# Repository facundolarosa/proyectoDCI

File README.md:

# proyectoDCI
Proyecto de la materia "Diseño de circuitos impresos"

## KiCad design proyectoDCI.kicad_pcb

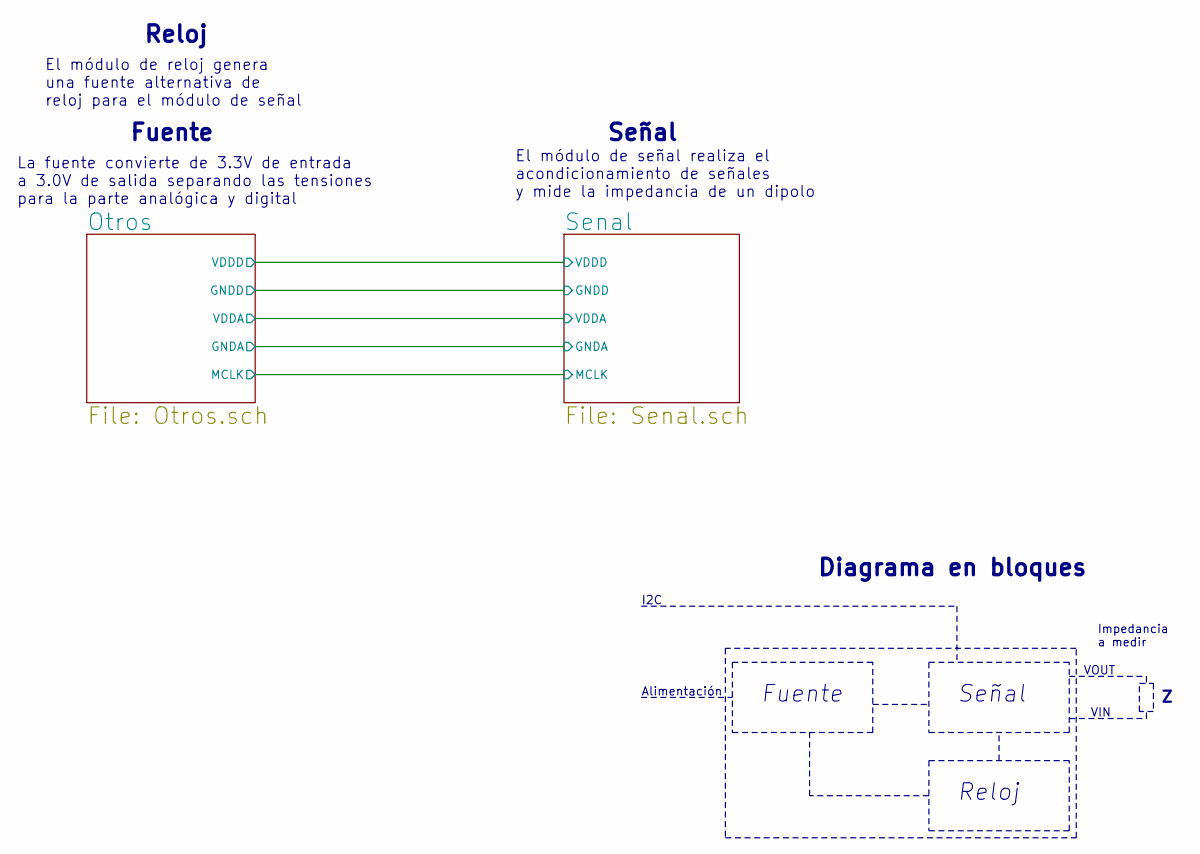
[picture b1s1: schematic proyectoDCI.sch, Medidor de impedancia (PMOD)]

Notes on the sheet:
Diagrama en bloques
Fuente
Señal
Reloj
VOUT
VIN
Impedancia a medir
I2C
La fuente convierte de 3.3V de entrada a 3.0V de salida separando las tensiones para la parte analógica y digital
El módulo de señal realiza el acondicionamiento de señales y mide la impedancia de un dipolo
El módulo de reloj genera una fuente alternativa de reloj para el módulo de señal
Alimentación

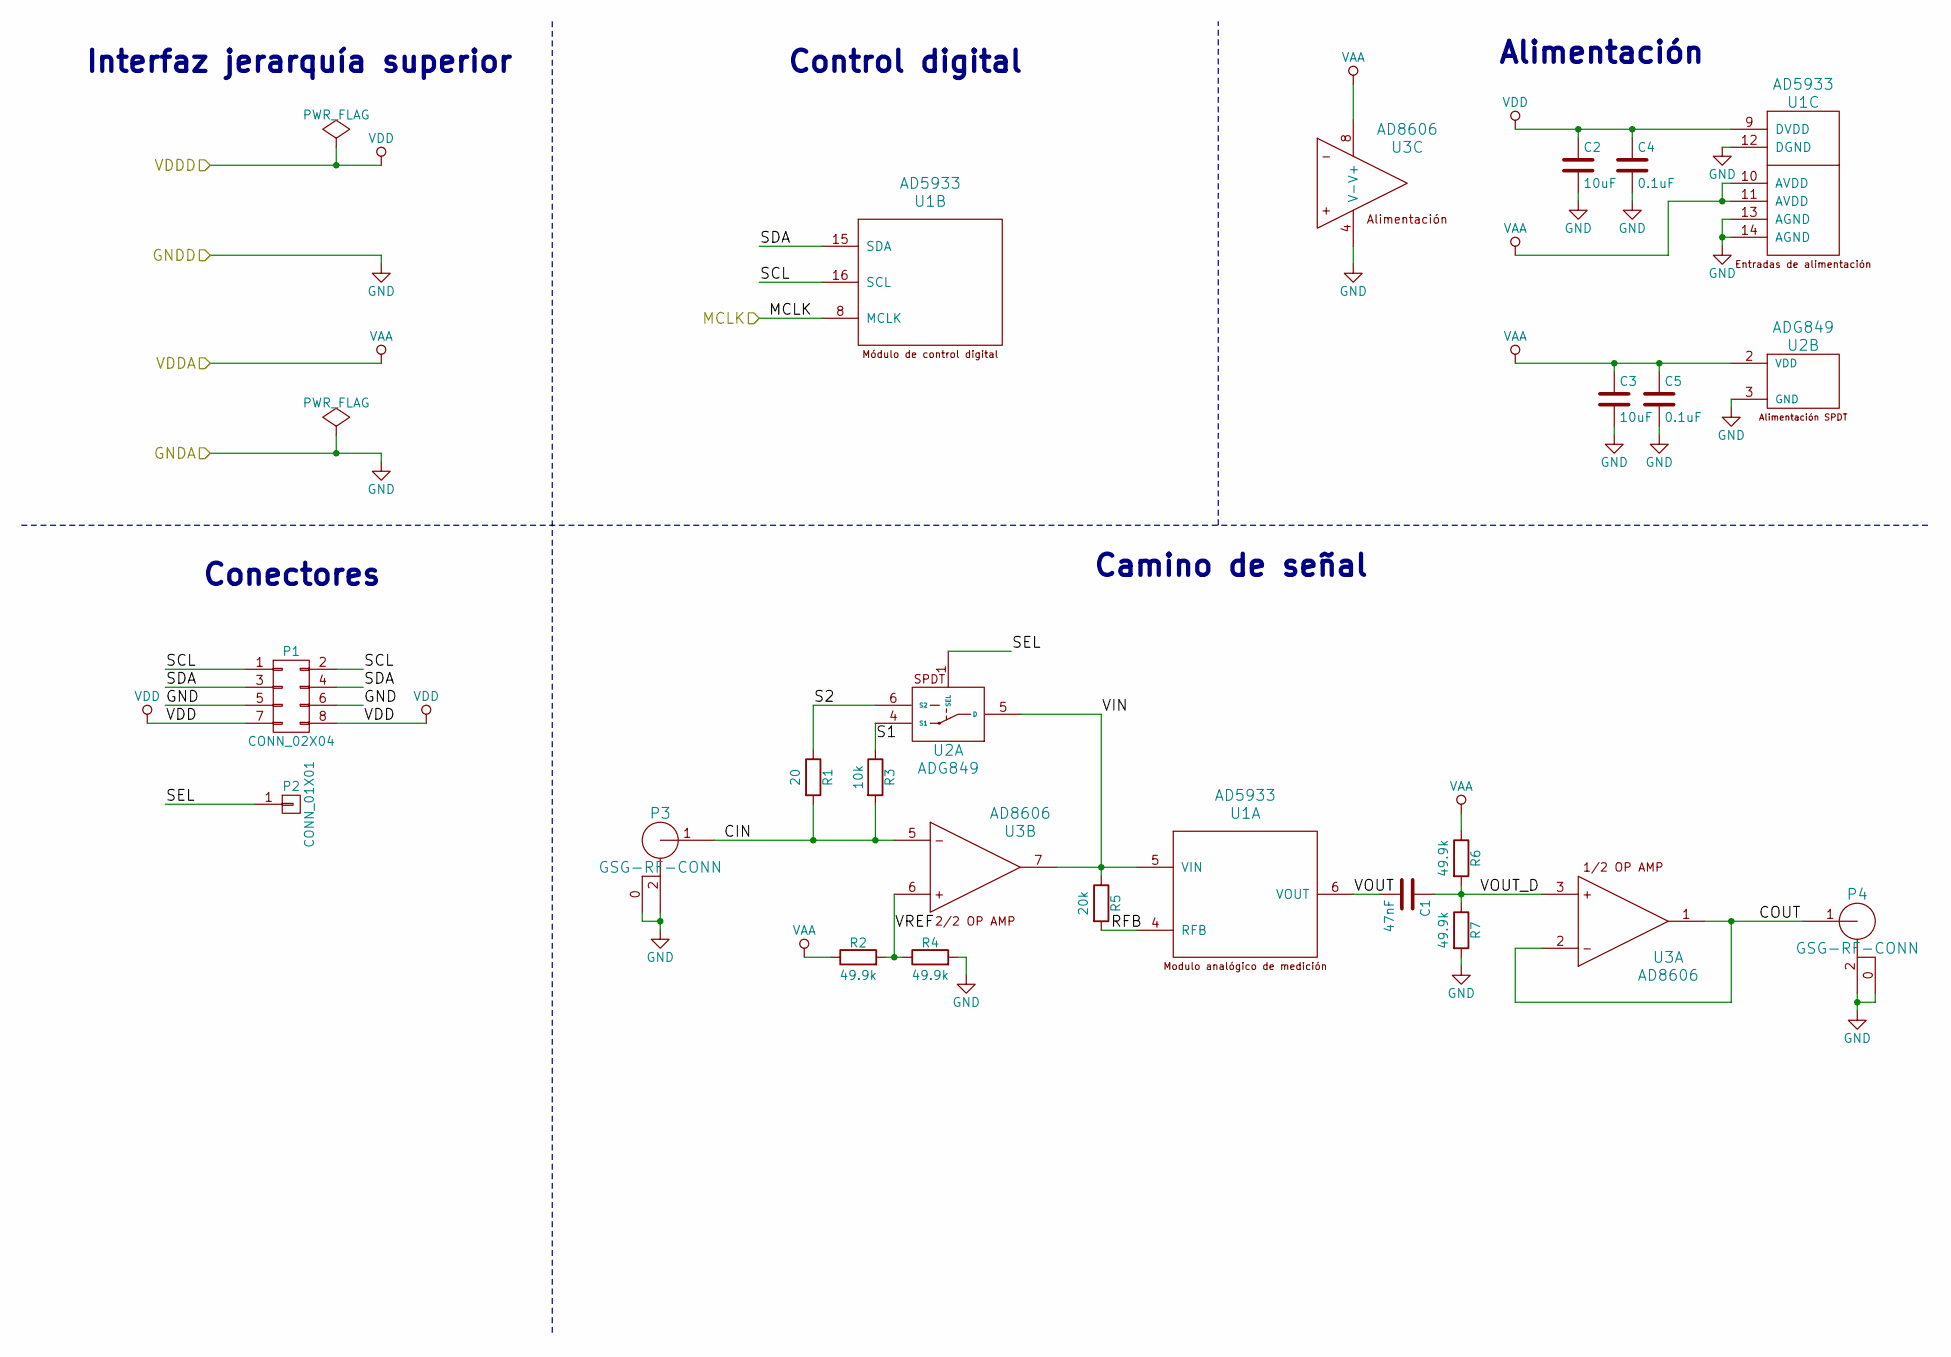
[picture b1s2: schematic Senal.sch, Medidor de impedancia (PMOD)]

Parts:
C1: 47nF; C_0603; Digikey# 478-1215-1-ND
C2, C3: 10uF; C_0603; Digikey# 478-1215-1-ND
C4, C5: 0.1uF; C_0603; Digikey# 478-1215-1-ND
P1: CONN_02X04; Pin_Header_Straight_2x04; Digikey# 609-3353-ND
P2: CONN_01X01; Pin_Header_Straight_1x01; Digikey# 732-5314-ND
P3, P4: GSG-RF-CONN; SMA_EDGE; Digikey# WM5534-ND
R1: 20; R_0603; Digikey# 311-10KGRTR-ND
R2, R4, R6, R7: 49.9k; R_0603; Digikey# 311-10KGRTR-ND
R3: 10k; R_0603; Digikey# 311-10KGRTR-ND
R5: 20k; R_0603; Digikey# 311-10KGRTR-ND
U1: AD5933; SSOP-16_5.3x6.2mm_Pitch0.65mm; Digikey# AD5933YRSZ-REEL7CT-ND
U2: ADG849; SC-70-6; Digikey# ADG849YKSZ-REEL7CT-ND
U3: AD8606; MSOP-8_3x3mm_Pitch0.65mm; Digikey# AD8606ARZ-ND

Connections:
/Otros/MCLK: U1.8 (MCLK); also elsewhere on the board
/Senal/CIN: P3.1 (RF), R1.2, R3.2, U3.5
/Senal/COUT: P4.1 (RF), U3.1, U3.2
/Senal/RFB: R5.2, U1.4 (RFB)
/Senal/S1: R3.1, U2.4 (S1)
/Senal/S2: R1.1, U2.6 (S2)
/Senal/SCL: P1.1, P1.2, U1.16 (SCL)
/Senal/SDA: P1.3, P1.4, U1.15 (SDA)
/Senal/SEL: P2.1, U2.1 (SEL)
/Senal/VIN: R5.1, U1.5 (VIN), U2.5 (D), U3.7
/Senal/VOUT: C1.2, U1.6 (VOUT)
/Senal/VOUT_D: C1.1, R6.2, R7.1, U3.3
/Senal/VREF: R2.2, R4.1, U3.6
GND: C2.2, C3.2, C4.2, C5.2, P1.5, P1.6, P3.0, P3.2 (GND), P4.0, P4.2 (GND), R4.2, R7.2, U1.12 (DGND), U1.13 (AGND), U1.14 (AGND), U2.3 (GND), U3.4 (V-); also elsewhere on the board
VAA: C3.1, C5.1, R2.1, R6.1, U1.10 (AVDD), U1.11 (AVDD), U2.2 (VDD), U3.8 (V+); also elsewhere on the board
VDD: C2.1, C4.1, P1.7, P1.8, U1.9 (DVDD); also elsewhere on the board

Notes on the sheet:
Alimentación
Interfaz jerarquía superior
Control digital
Camino de señal
Conectores

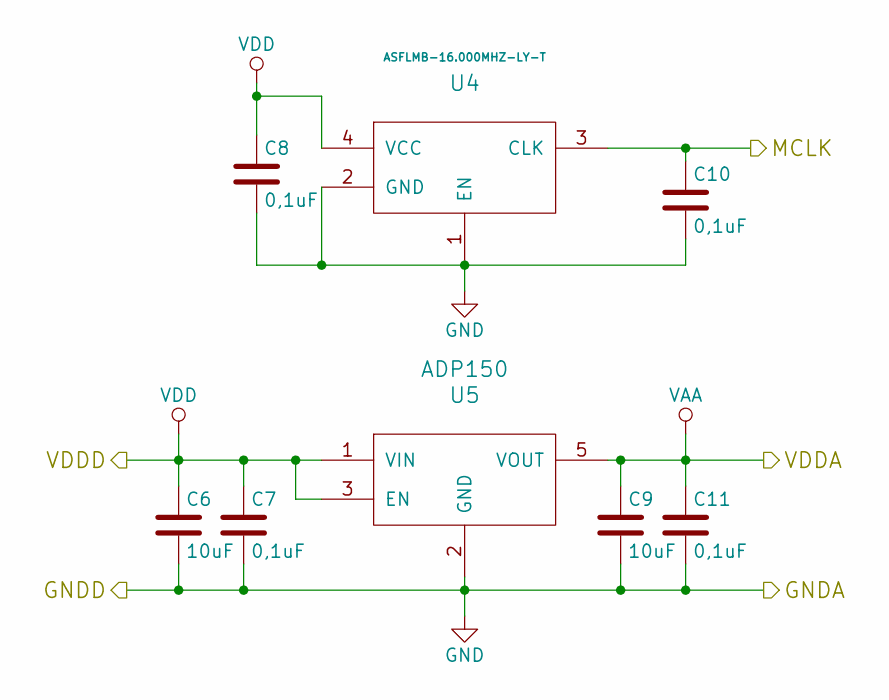
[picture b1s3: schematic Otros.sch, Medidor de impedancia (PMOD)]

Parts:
C6, C9: 10uF; C_0603; Digikey# 478-1215-1-ND
C7, C8, C10, C11: 0,1uF; C_0603; Digikey# 478-1215-1-ND
U4: ASFLMB-16.000MHZ-LY-T; TCXO; Digikey# 535-10987-1-ND
U5: ADP150; SC-70-5; Digikey# ADP150AUJZ-1.8-R7CT-ND

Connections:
/Otros/MCLK: C10.1, U4.3 (CLK); also elsewhere on the board
GND: C6.2, C7.2, C8.2, C9.2, C10.2, C11.2, U4.1 (EN), U4.2 (GND), U5.2 (GND); also elsewhere on the board
VAA: C9.1, C11.1, U5.5 (VOUT); also elsewhere on the board
VDD: C6.1, C7.1, C8.1, U4.4 (VCC), U5.1 (VIN), U5.3 (EN); also elsewhere on the board

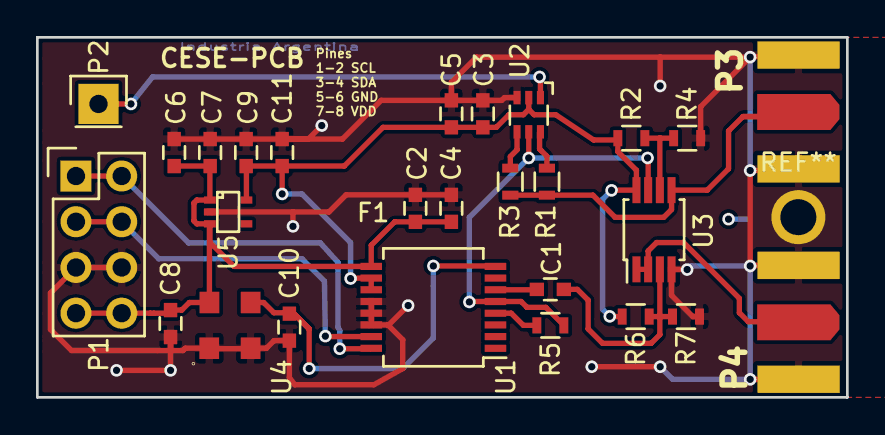
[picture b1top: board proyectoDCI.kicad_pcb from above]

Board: 2 copper layers, 45.0 x 20.0 mm, 28 parts (0 on the bottom side), 16 nets.

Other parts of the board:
F1: Fiducial_1mm_Dia_2.54mm_Outer_CopperTop

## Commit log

2016-11-17 Se creo la estructura básica de directorios. Se agregaron los esquematicos, hojas de datos del diseño de referencia y requerimientos.
2016-11-17 Se agrego el estandar de fabricacion a utilizar (/doc/fab)
2016-11-17 Se agregaron hojas de datos adicionales. Se describió el proyecto y sus módulos en general en la memoria
2016-11-17 Se inicio el esquematico. Se dibujo el diagrama en bloques y las hojas jerarquicas.
2016-11-17 Se termino el diagrama general y se agrego texto explicativo.
2016-11-17 Se agregaron los simbolos para: regulador y medidor de impedancia
2016-11-18 Se terminaron todos los simbolos necesarios. Se realizo el esquematico de la fuente y el reloj. Se inicio el esquematico de la parte de señal.
2016-11-18 Se trabajo sobre la hoja de señal. Se terminó el esquemático, salvo que resta agregar los conectores.
2016-11-25 Agregados los conectores. Finalizado el esquemático
2016-11-25 Se enlazaron los simbolos con los footprint. Se agregó una librería con conectores SMA.
2016-11-25 Footprints creados y linkeados. Listo para proceder al PCB. Todas las DRC dan OK
2016-11-25 Placement inicial en base a componentes por cercania
2016-11-25 Se modificó el esquemático para cumplir con las correcciones propuestas. Resta modificar el rótulo y el símbolo de resistor. Agregar campos KiCost
2016-11-25 Reformulado el esquematico para contener el diseño en dos hojas
2016-12-02 Se agregaron los campos Digikey#
2016-12-09 Problema de footprints solucionado
2016-12-09 Sectorizacion terminada
2016-12-09 Se achico el tamaño de la placa para hacerla mas compacta
2016-12-09 Se achico nuevamente la placa y se acomodo la serigrafia
2016-12-09 Antes de comenzar a rutear. Reglas cargadas
2016-12-09 Ruteados los conjuntos por separado
2016-12-10 Ruteo completado
2016-12-10 Solucionados todos los problemas de DRC
2016-12-10 Se agrego la silueta del TCXO y se corrigieron los footprints de los SMA
2016-12-10 Se modifico el rotulo y se agregaron aclaraciones del proceso de fabricacion
2016-12-10 Se agrego leyenda del proyecto y vias adicionales para unir los planos de tierra
2016-12-10 Se quitaron librerias sobrantes y se actualizaron los footprints a kicad_mod
2016-12-14 Corregido error de tipeo en REQUERIMIENTOS DEL PROYECTO
2016-12-24 Correcciones sugeridas por la 2da revision efectuada por D. Brengi
